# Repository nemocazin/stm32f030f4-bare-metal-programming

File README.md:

# STM32F030F4 Bare metal programming

## Table of content

 * [General project information](#general-project-information)
 * [Electronic board design](#electronic-board-design)
 * [Embedded programming and test design](#embedded-programming-and-test-design)
 * [Contact](#contact)

## General project information

This product was developed as part of a fourth-year project in the Embedded Systems program at Polytech Lille with an another student. It consisted in designing an electronic board to measure temperature and store the values in an EPROM-type memory. We had to create the board and the programming ourselves, __in a context of mass production__. As a result, we had to work as if we were in a company, meaning we had to carry out all the design stages of a product. 

__This project is focused on the test and maintenance part of the project__. Whether we were testing the physical board or the programming part, we had to do our best to ensure that the board worked in spite of the environment and all its constraints.

The project is therefore divided in __two parts__ : the physical part with the electronic board, and the programming part with the embedded program and the tests carried out on it.

## Electronic board design

This part consists of designing the electronic board. The purpose of this board is to __measure temperature and store measured values in an EPROM-type memory__. We were then asked to design certain components, such as the temperature sensor. 

We then designed the board on Kicad-6 and drew up the schematic and routing. In the end, the board was designed on Polytech Lille's site, from manufacturing to soldering.

We also carried out tests on the board to see how it performed in certain types of environment. 

The board design files can be found in the _"PCB"_ folder of the current directory.

## Embedded programming and test design

The programming of the card was mainly __carried out in the C programming language and using bare metal programming__.

We also used the _"check.h"_ library to carry out unit tests and ensure the proper functioning of our code.

Nucleo boards were available to transfer our file to our microcontroller

## Contact

Created by [@nemocazin] & Antoine Cegarra

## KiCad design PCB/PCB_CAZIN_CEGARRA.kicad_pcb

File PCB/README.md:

# STM32F030F4 Bare metal programming
# __PCB Conception Part__

## Table of content

 * [General project information](#general-project-information)
 * [Schematic design](#cchematic-design)
    * [STM32F030F4 ARM Cortex microcontroller configuration](#stm32f030f4-arm-cortex-microprocessor-configuration)
    * [M24C01 EPROM memory configuration](#m24c01-eprom-memory-configuration)
    * [MCP9700 temperature sensor configuration](#mcp9700-temperature-sensor-configuration)
    * [ARM JTAG connector configuration](#arm-jtag-connector-configuration)
    * [Other components](#other-components)
    * [Decoupling capacitors](#decoupling-capacitors)
    * [TestPoints documentation](#testpoints-documentation)
 * [PCB design](#pcb-design)
 * [Gerber files](#gerber-files)
 * [Soldering](#soldering)
 * [Documentation used](#documentation-used)
 * [Contact](#contact)

## General design information

This project enabled us to design an electronic board for mass production. This put us in a real design situation, so we had to be rigorous in our work and explanations.
For the design of this electronic board, several components were imposed on us. Firstly, the microcontroller is an __STM32F030F4 Arm Cortex__ with a 32-bit RISC-V core. Next, we had to use a __1kbit M24C01 EPROM memory__ on the I2C serial bus. Last but not least, a __Low-Power Linear Active MCP9700 temperature sensor__ was required.
With this information on the components we needed, we began the schematic of our board.

## Schematic design

### STM32F030F4 ARM Cortex microcontroller configuration

As we're using an ARM Cortex microcontroller, we had to do a lot of research to create the schematic around this component. First of all, the __NRST pin__ corresponds to the reset and a 0.1uF capacitor is connected. This information comes from the microcontroller documentation, so we did the same. 
The __BOOTO pin__ is used to control the microcontroller's start-up mode. _When the pin is in the low state (0)_, the microcontroller starts normally from its internal flash memory, where the user program is stored. On the contrary, _when the pin is high (1)_, the microcontroller starts up in special boot mode. This means it will attempt to boot from a different boot source, such as a connected programming device (like an ST-Link or bootloader), or from external memory (like separate flash memory). We've therefore chosen to connect this pin to a 3-pin connector linked to VCC or GND, so as to manually select the microcontroller's start-up mode. This can be seen as manual debugging.
__Pins PF0 and PF1__ correspond to clock management, for which we also used the microcontroller documentation which gave us the schematic. We also used an 8MHz quartz clock, which is the microcontroller frequency.

### M24C01 EPROM memory configuration

To manage the M24C01 EPROM memory component, several pins are connected directly to the microcontroller input/output pins: 
 - __The SDA pin__ is used to transmit data between the EEPROM and the master device. Data to be written to or read from the EEPROM are transmitted via this line. It is linked to pin PA10 of the microcontroller, corresponding to I2C management from master to slave.
 - __The SCL pin__ provides a synchronization clock for serial communication between the EEPROM and the master device. This clock ensures that data is transmitted and received synchronously between the peripherals. It is connected to pin PA9 of the microcontroller.
 - __Pins E0, E1 and E2__ on an EPROM are used to configure the device address. These pins define the EPROM address on the I2C bus. When one of the pins is connected to ground (GND), it sets the least significant bit of the EPROM address to 0. If it is left floating or connected to a high voltage (VCC), it will set this bit to 1. These pins are then connected to pins PA4, PA3, PA2 of the microcontroller.
 - __Pin WC__ controls memory write protection. _When pin WC is held low (0)_ or connected to ground (GND), this indicates that memory write protection is enabled. This means that EEPROM write operations are disabled or protected from modification. On the other hand, _when pin WC is held high (1)_ or connected to a supply voltage (VCC), this indicates that write protection is disabled, allowing normal write operations on the EEPROM memory. This pin is also connected to pin PA7 of the microcontroller. We've also added a 3-pin connector for manual debugging.
This component also operates at 5V, so it is connected directly to VCC for power supply.
Pull-up resistors have been added to initialize the SDA, SCL and EPROM pins to the high state when the electronic board is powered up. This prevents random data from being written to memory. 

### MCP9700 temperature sensor configuration

The MCP9700 temperature sensor is easy to use. __A single output pin named TEMP__ gives the temperature value at several voltage levels. We connected it to the PA1 input/output pin of the microcontroller. This component also operates at 5V, so it's connected directly to VCC for power supply.

### ARM JTAG connector configuration

This connector allows you to control the power supply to the electronic board, as well as program the microntrolleur and perform simple debugging. This component operates at 5V, so it's connected directly to VCC for power supply.
We use two pins for this component: 
 - __The SWDIO pin__ is used to transmit data between the debugger and the microcontroller. This is a bidirectional data line where debug instructions, programming data and read data can be transmitted in both directions. We then connected it to the PA13 input/output pin of the microcontroller.
 - __The SWDCLK pin__ is used to synchronize communication between the debugger and the microcontroller. This clock ensures that data is transmitted synchronously and consistently between the two devices. We then connected it to the PA14 input/output pin on the microcontroller.

### Other components

We've added __two debugging LEDs__ on pins PA0 and PA5 of the microcontroller.

### Decoupling capacitors

The imposed components need decoupling capacities in order to function correctly: 
 - the STM32F030F4 microcontroler needs __5 decoupling capacitors__: C4 at 1uF, C5 at 10nF, C6 at 100nF, C8 at 4.7uF and C10 at 100nF.
 - the M24C01 serial EEPROM memory requires __one decoupling capacitor__ C9 at 100nF.
 - the MCP9700 temperature sensor requires __one decoupling capacitor__ of C7 at 1uF.

### TestPoints documentation

We've added testpoints to check the voltages of certain critical tracks, and also to potentially add additional components. These testpoints also serve as a means of debugging: 
 - __TP1__ is connected to the PB1 input/output pin to potentially add a component
 - __TP2__ is connected to the microcontroller's VCC pin to monitor the voltage value and modify it if necessary
 - __TP3__ is connected to input/output pin PA6 to potentially add a component
 - __TP4__ is connected to the temperature sensor's temperature output pin to monitor output voltage values
 - __TP5__ is connected to the EPROM pin of the EPROM to check voltage and also control EPROM protection manually
 - __TP6__ is connected to the SWCLK pin of the JTAG connector to check synchronization clock voltages 
 - __TP7__ is connected to the SWCLK pin of the JTAG connector if data is being transmitted

## PCB design

For the creation of the PCB, we wanted to do mostly single-sided to facilitate production. In the end, we had to make a track on the underside.
For component footprints other than those specified, we used those from the SparkFun library. 
To place the components, we assembled them together as shown in the schematic. We also grouped the testpoints together to facilitate debugging. Component decoupling capabilities have also been glued to the respective components.
Long tracks for VCC and GND run around the board, which is not optimized but will work in our application.
The result is a 47x40 mm board, with a ground plane on each side.

## Gerber files

We left the Gerber files in the directory in a ZIP file. These are used to create the stencils for the electronic board. These files can be used on a Gerber Viewer like site : [Gerber Viewer](https://www.pcbway.com/project/OnlineGerberViewer.html); 

## Soldering

We soldered the components to the board using tin. As the components are very small, soldering them was a bit tricky.
Here's the soldered board :

## Documentation used

* _[STM32F030F4 microcontroler](https://www.st.com/en/microcontrollers-microprocessors/stm32f030f4.html)_
* _[STM32F030F4 microcontroller hardware consideration](https://www.google.com/url?sa=t&rct=j&q=&esrc=s&source=web&cd=&ved=2ahUKEwjCvNPB3rKEAxWJRqQEHd2wAtIQFnoECA4QAQ&url=https%3A%2F%2Fwww.st.com%2Fresource%2Fen%2Fapplication_note%2Fan4325-getting-started-with-stm32f030xx-and-stm32f070xx-series-hardware-development-stmicroelectronics.pdf&usg=AOvVaw3LE5Z_h3sACrHhfwqq26Si&opi=89978449)_
* _[M24C01 serial EEPROM memory](https://www.st.com/en/memories/m24c01-r.html)_
* _[MCP9700 temperature sensor](https://www.microchip.com/en-us/product/mcp9700)_
* _[MCP9700 temperature sensor hardware consideration](http://ww1.microchip.com/downloads/en/devicedoc/20001942g.pdf)_

## Contact

Created by [@nemocazin] & Antoine Cegarra

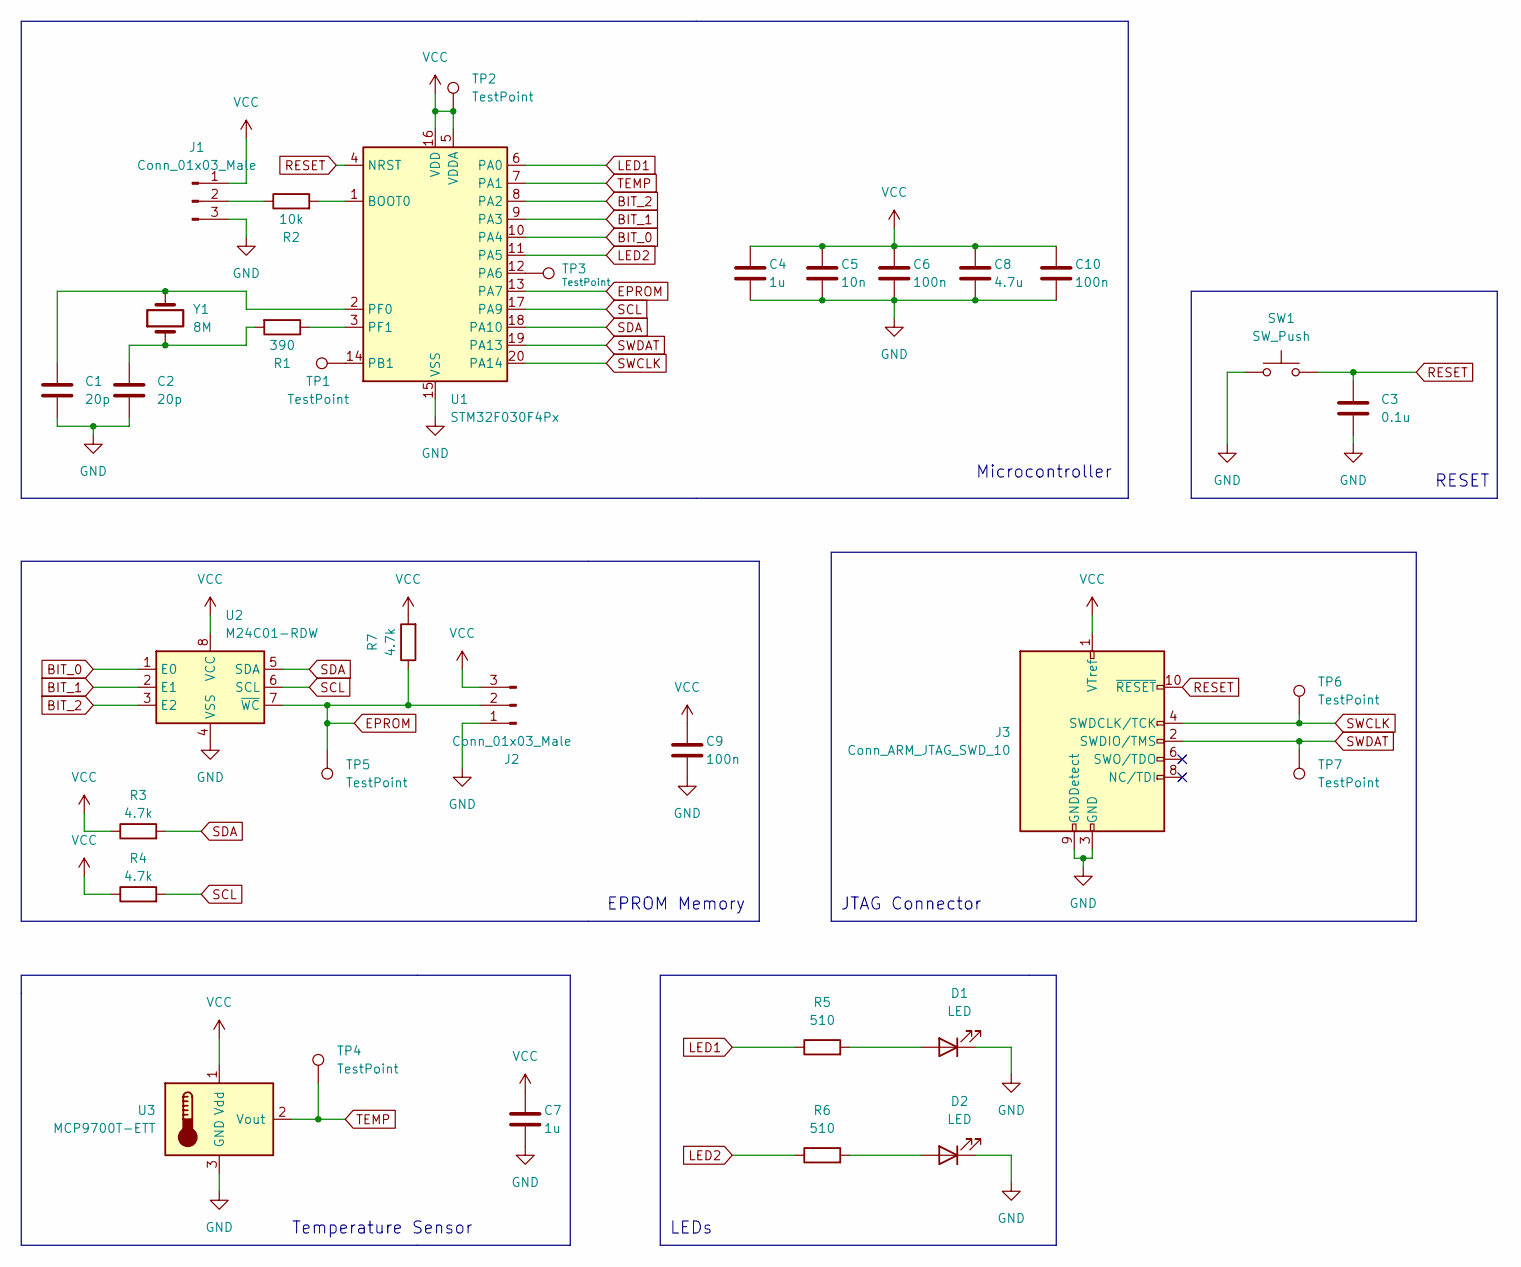
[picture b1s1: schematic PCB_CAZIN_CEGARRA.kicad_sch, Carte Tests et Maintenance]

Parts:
C1, C2: 20p; C_0603_1608Metric_Pad1.08x0.95mm_HandSolder
C3: 0.1u; C_0603_1608Metric_Pad1.08x0.95mm_HandSolder
C4, C7: 1u; C_0603_1608Metric_Pad1.08x0.95mm_HandSolder
C5: 10n; C_0603_1608Metric_Pad1.08x0.95mm_HandSolder
C6, C9, C10: 100n; C_0603_1608Metric_Pad1.08x0.95mm_HandSolder
C8: 4.7u; C_0603_1608Metric_Pad1.08x0.95mm_HandSolder
D1, D2: LED; LED_0603_1608Metric_Pad1.05x0.95mm_HandSolder
J1, J2: Conn_01x03_Male; PinHeader_1x03_P1.00mm_Vertical
J3: Conn_ARM_JTAG_SWD_10; PinHeader_2x05_P2.54mm_Vertical
R1: 390; R_0603_1608Metric_Pad0.98x0.95mm_HandSolder
R2: 10k; R_0603_1608Metric_Pad0.98x0.95mm_HandSolder
R3, R4, R7: 4.7k; R_0603_1608Metric_Pad0.98x0.95mm_HandSolder
R5, R6: 510; R_0603_1608Metric_Pad0.98x0.95mm_HandSolder
SW1: SW_Push; TACTILE_SWITCH_SMD_5.2MM
TP1, TP2, TP3, TP4, TP5, TP6, TP7: TestPoint; TestPoint_Pad_D1.5mm
U1: STM32F030F4Px; TSSOP-20_4.4x6.5mm_P0.65mm
U2: M24C01-RDW; TSSOP-8_4.4x3mm_P0.65mm
U3: MCP9700T-ETT; SOT-23
Y1: 8M; Crystal_SMD_HC49-SD

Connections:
BIT_0: U1.10 (PA4), U2.1 (E0)
BIT_1: U1.9 (PA3), U2.2 (E1)
BIT_2: U1.8 (PA2), U2.3 (E2)
EPROM: J2.2, R7.1, TP5.1, U1.13 (PA7), U2.7 (~WC)
GND: C1.2, C2.2, C3.2, C4.2, C5.2, C6.2, C7.2, C8.2, C9.2, C10.2, D1.1 (K), D2.1 (K), J1.3, J2.1, J3.3 (GND), J3.5 (GND), J3.9 (GNDDetect), SW1.1, U1.15 (VSS), U2.4 (VSS), U3.3 (GND)
LED1: R5.1, U1.6 (PA0)
LED2: R6.1, U1.11 (PA5)
unnamed: C1.1, U1.2 (PF0), Y1.2
unnamed: C2.1, R1.2, Y1.1
unnamed: D1.2 (A), R5.2
unnamed: D2.2 (A), R6.2
unnamed: J1.2, R2.1
unnamed: R1.1, U1.3 (PF1)
unnamed: R2.2, U1.1 (BOOT0)
unnamed: TP1.1, U1.14 (PB1)
unnamed: TP3.1, U1.12 (PA6)
RESET: C3.1, J3.10 (~RESET), SW1.2, U1.4 (NRST)
SCL: R4.2, U1.17 (PA9), U2.6 (SCL)
SDA: R3.2, U1.18 (PA10), U2.5 (SDA)
SWCLK: J3.4 (SWDCLK/TCK), TP6.1, U1.20 (PA14)
SWDAT: J3.2 (SWDIO/TMS), TP7.1, U1.19 (PA13)
TEMP: TP4.1, U1.7 (PA1), U3.2 (Vout)
VCC: C4.1, C5.1, C6.1, C7.1, C8.1, C9.1, C10.1, J1.1, J2.3, J3.1 (VTref), R3.1, R4.1, R7.2, TP2.1, U1.5 (VDDA), U1.16 (VDD), U2.8 (VCC), U3.1 (Vdd)

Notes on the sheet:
RESET
Microcontroller
EPROM Memory
Temperature Sensor
JTAG Connector
LEDs

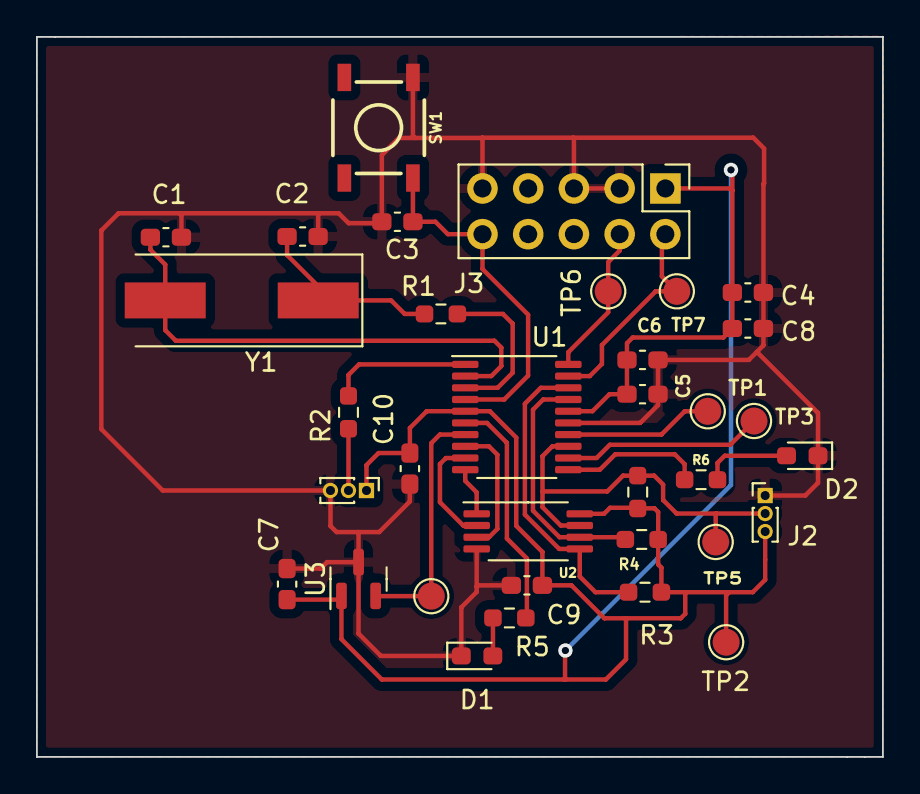
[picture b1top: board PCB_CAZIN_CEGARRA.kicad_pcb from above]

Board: 2 copper layers, 47.0 x 40.0 mm, 34 parts (0 on the bottom side), 23 nets.

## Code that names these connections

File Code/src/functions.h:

/**
 * @brief      This file contains all the register addresses and function prototypes used.
 *
 * @author     Némo CAZIN & Antoine CEGARRA
 * @date       2024
 */
#include <stdio.h>
#include <stdint.h>

/**
 * @details These defines are used for testing. If the program is run on a computer (X86), 
 *          the defines replace those of the volatile type used for the microcontroller.
 */
#if defined(__x86_64__) || defined(_M_X64)

#define GPIOA_BASE      0x48000000
extern  uint32_t        GPIOA_MODER;
extern  uint32_t        GPIOA_IDR;
extern  uint32_t        GPIOA_ODR;
#define GPIOA_INPUT     0UL
#define GPIOA_OUTPUT    1UL

#else
// Memory mapped addresses for GPIO
#define GPIOA_BASE      0x48000000 
#define RCC_BASE        0x40021000 

// RCC registers
#define RCC_AHBENR      (*(volatile uint32_t *)(RCC_BASE + 0x14))
#define RCC_APB2ENR     (*(volatile uint32_t *)(RCC_BASE + 0x18))

// GPIO registers
#define GPIOA_MODER     (*(volatile uint32_t *)(GPIOA_BASE + 0x00)) //I/O pins configuration
#define GPIOA_IDR       (*(volatile uint32_t *)(GPIOA_BASE + 0x10)) //Input 
#define GPIOA_ODR       (*(volatile uint32_t *)(GPIOA_BASE + 0x14)) //Output
#define GPIOA_INPUT     0UL
#define GPIOA_OUTPUT    1UL
#define GPIOAEN         (1 << 17) // I/O port A clock enable

#endif

// Pins
#define LED1            0
#define TEMP            1
#define BIT2            2
#define BIT1            3
#define BIT0            4
#define LED2            5
#define EPROM           6
#define SCL             7
#define SDA             10
#define SWDAT           13
#define SDCLK           14

#define TWO_BITS        2
#define ON              1UL
#define OFF             1UL

// Prototypes

/**
* @brief Create a delay with a for loop
* 
* @return Number of iterations
*/
uint32_t delay (uint32_t iterations);


/**
* @brief Configures the register GPIOA_MODER to set LED1 to output
* 
* @return 1
*/
uint32_t LED1_config (void);


/**
* @brief Configures the register GPIOA_ODR to turn off LED1
* 
* @return 1
*/
uint32_t LED1_off (void);


/**
* @brief Configures the register GPIOA_ODR to turn on LED1
* 
* @return 1
*/
uint32_t LED1_on (void);


/**
* @brief Blink LED1
* 
* @return 1
*/
uint32_t LED1_blink (void);


/**
* @brief Configures the register GPIOA_MODER to set LED2 to output
* 
* @return 1
*/
uint32_t LED2_config (void);


/**
* @brief Configures the register GPIOA_ODR to turn off LED2
* 
* @return 1
*/
uint32_t LED2_off (void);


/**
* @brief Configures the register GPIOA_ODR to turn on LED2
* 
* @return 1
*/
uint32_t LED2_on (void);


/**
* @brief Blink LED2
* 
* @return 1
*/
uint32_t LED2_blink (void);


/**
* @brief Configures the register GPIOA_MODER to set the temperature sensor to input
* 
* @return 1
*/
uint32_t temp_sensor_config (void);


/**
* @brief Converts the voltage recovered from the temperature sensor into °C
* 
* @return The temperature (float)
*/
uint32_t temperature_conversion (uint32_t analogVoltageValue);

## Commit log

2024-08-01 [transfer] : Gitlab to Github
2024-08-01 [add] : CI jobs
2024-08-01 [fix] : routes to make
2024-08-01 [add] : badges and new coverage task
2024-08-01 [fix] : yml line 10 syntax
2024-08-01 [fix] : branch yml
2024-08-01 [fix] : README badges
